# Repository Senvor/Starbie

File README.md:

<div align="center">

# Starbie

**A tiny motion-controlled digital pet, basically a desktop Tamagotchi. Totally not a Starboy.**

A star-shaped PCB pet you tilt, shake and feed, with an OLED face, a mood LED and two clicky switches.

</div>

---

## What is it?

Starbie is a small interactive device built around the XIAO ESP32-C3. It uses a bunch of sensors and other components to make it actually do stuff.

Some of the things packed into it:

- **Movement detection** using the MPU6050, so you steer the menu by tilting and play by shaking
- **Temperature and humidity** readings from the DHT11
- **An OLED display** for the pet, the menu and the stats
- **An RGB LED** that shows the pet's mood
- **Two mechanical switches** (Gateron Milky Pro Yellow with Cherry-style keycaps) for input
- **Stats saved to flash**, so your pet remembers you after a reset

## Why I Built It

I made Starbie for [HalfLife](https://halflife.hackclub.com), following their Week 1 PCB design tutorial.

Since this is my second hardware project, I wanted to build something a bit more interesting than my first one. Starbie is a tiny motion-controlled digital pet, basically a desktop Tamagotchi (totally not a Starboy).

And yeah, I'm also trying to get that 3D printer prize lol. HalfLife gives me a reason to actually design, build and document my projects instead of leaving them as ideas.

The full build log is in [JOURNAL.md](JOURNAL.md).

## The Schematic

The schematic was made in KiCad and shows how all the components are connected to the XIAO ESP32-C3.

<div align="center">

</div>

## The PCB Design

I designed the board using KiCad, with a custom shape and footprints for the components.

<div align="center">
  
</div>

## Fabrication

Here's the final manufacturing quote and preview from Robu before it becomes reality:

<div align="center">
    
</div>

## Firmware

The firmware is written for the XIAO ESP32-C3 and handles Starbie's sensors, display, RGB LED and buttons. It reads movement data from the MPU6050 and temperature and humidity from the DHT11, with the OLED used to display information.

### Wiring (pins)

| Part | XIAO pin | ESP32-C3 GPIO |
|---|---|---|
| OLED + MPU6050 SDA | D5 | 7 |
| OLED + MPU6050 SCL | D4 | 6 |
| DHT11 data | D1 | 3 |
| Button 1 | D2 | 4 |
| Button 2 | D3 | 5 |
| LED red | D0 | 2 |
| LED green | D6 | 21 |
| LED blue | D7 | 20 |

The RGB LED is common anode (tied to 3.3V), so the firmware drives a colour LOW to turn it on. The OLED is expected at I2C address `0x3C` and the MPU6050 at `0x68`.

### Controls

Starbie has two buttons.

| Button | Pin | What it does |
|---|---|---|
| Button 1 (SW1) | GPIO4 (XIAO D2) | Opens the radial menu. While the menu is open, it confirms the highlighted action. |
| Button 2 (SW2) | GPIO5 (XIAO D3) | Shows or hides the stats screen. It never changes the pet. |

Both buttons are debounced in software (30 ms).

### Tilt menu

1. Press **Button 1** to open the menu. The way you are holding Starbie at that moment becomes the centre.
2. Tilt Starbie. The MPU6050 accelerometer moves a ball around the screen. The screen is split into four sectors by two diagonal lines: **NAP** (top), **PLAY** (right), **FEED** (bottom) and **PET** (left).
3. The sector in the direction you tilt is highlighted. A small dead zone in the middle means nothing is highlighted until you tilt past it.
4. Press **Button 1** again to confirm. If nothing is highlighted, nothing happens and the menu stays open.
5. Pressing **Button 2** while the menu is open leaves the menu without choosing anything and shows the stats screen instead.

Which physical tilt direction moves the ball to which sector depends on how the MPU6050 is mounted. If the ball moves the wrong way, change `SWAP_MPU_AXES`, `MENU_X_DIRECTION` or `MENU_Y_DIRECTION` at the top of `Starbie.ino`.

Each action changes the pet's three stats (each stays between 0 and 100):

| Action | Joy | Energy | Fullness | What you see |
|---|---|---|---|---|
| NAP | +1 | +18 | −4 | Starbie stops and sleeps with floating Zs for 48 seconds |
| PLAY | +12 | −9 | −5 | Two fast laps across the screen with hearts |
| FEED | +3 | +2 | +18 | A small wiggle, then a jump |
| PET | +7 | 0 | 0 | A small wiggle, a jump, and hearts |

**Shake:** on the pet screen, shaking Starbie gives +5 joy, −2 energy and −1 fullness, wakes a sleeping pet, and has a 0.65 second cooldown. Shaking does nothing while the menu or stats screen is open.

Stats are saved to flash after every action and every shake, so Starbie remembers them after a reset. Stats do not drain over time; they only change when you use the menu or shake Starbie.

### Status LED

The RGB LED shows Starbie's mood. The firmware checks the stats in this order and shows the first one that matches:

| Colour | Condition | Meaning |
|---|---|---|
| Yellow | Fullness is 25 or below | Hungry |
| Blue | Energy is 25 or below | Tired |
| Red | Joy is 25 or below | Needs play |
| Green | None of the above (all three stats are above 25) | Happy |

If more than one stat is low, the first row that matches wins (yellow, then blue, then red). The LED is on/off only (no dimming or colour mixing), and yellow is red and green on together.

### Stats screen

Press **Button 2** to see Starbie's JOY, ENERGY and FULL bars with their numbers, plus the room temperature (°C) and humidity (%) from the DHT11. If the DHT11 has not produced a reading yet, the screen shows `--`. The temperature and humidity are display-only; they do not affect the pet or the LED.

## Getting Started

The firmware is one file, `Starbie.ino`.

1. Open `Starbie.ino` in the [Arduino IDE](https://www.arduino.cc/en/software) with ESP32 board support installed, and pick the **Seeed XIAO ESP32-C3** board.
2. Install these libraries from **Sketch > Include Library > Manage Libraries** (click **Install All** when it asks about dependencies):
   - Adafruit GFX Library
   - Adafruit SSD1306
   - Adafruit MPU6050
   - DHT sensor library
3. Change anything you want in the **BEGINNER SETTINGS** section at the top (pins, starting stats, tilt directions, the pet sprite).
4. Upload.

Want a fresh pet? Set `RESET_SAVED_PET_ON_BOOT` to `true`, upload once, then set it back to `false`.

## Bill Of Materials

Also in [BOM.csv](BOM.csv).

| Item | Qty | Supplier | Cost/item | Total Cost | Link |
|---|---:|---|---:|---:|---|
| XIAO ESP32-C3 | 1 | hubtronics | $7.17 | $7.17 | https://hubtronics.in/seeed-studio-xiao-esp32c3 |
| MPU-6050 GY-521 | 1 | hubtronics | $2.00 | $2.00 | https://hubtronics.in/gy-521-mpu-6050-gyro-accelerometer-module |
| 5mm RGB LED, 4-leg (pack of 5) | 1 | hubtronics | $0.32 | $0.32 | https://hubtronics.in/5mm-rgb-led-4-legs |
| 0.96-inch I2C OLED, white | 1 | hubtronics | $1.78 | $1.78 | https://hubtronics.in/0.96inch-i2c-4pin-oled-module-white |
| Blank translucent Cherry 1u keycaps (pack of 5) | 1 | meckeys | $1.36 | $1.36 | https://meckeys.com/shop/accessories/keyboard-accessories/keycaps/blank/blank-ch |
| Gateron Milky Pro Yellow 5-pin switches (pack of 10) | 1 | meckeys | $2.10 | $2.10 | https://meckeys.com/shop/accessories/keyboard-accessories/key-switches/gateron-mechanical-pro-switch-5pin/?attribute_pa_switch-variation=pro-milky-yellow |
| 330Ω, 1/8W resistor (pack of 42) | 1 | robu | $0.11 | $0.11 | https://robu.in/product/330-ohm-1-8w-through-hole-resistor-pack-of-5000/ |
| 10kΩ, 1/8W resistor (pack of 30) | 1 | robu | $0.11 | $0.11 | https://robu.in/product/10k-ohm-0-25w-metal-film-resistor-pack-of-100/ |
| DHT11 temperature and humidity sensor | 1 | robu | $1.57 | $1.57 | https://robu.in/product/dht-11-digital-temperature-and-humidity-sensor/ |
| Custom Starbie PCB | 1 | robu | $20.05 | $20.05 | https://robu.in/ |
| Total shipping | 1 | — | — | $2.38 | — |

## Tech Stack

- **KiCad** - schematic and PCB design
- **Robu** - PCB fabrication quote and preview
- **Arduino (C++)** - the firmware
- **Seeed XIAO ESP32-C3** - the brain
- **Adafruit GFX / SSD1306 / MPU6050 + DHT sensor library** - display and sensor drivers
- **Preferences (ESP32)** - saving the pet's stats to flash

## Project Structure

```
Starbie/
├── Starbie.ino       # the whole firmware, one file
├── pcb/              # KiCad project, schematic and PCB
├── output files/     # fabrication outputs (Starbie.zip)
├── assets/           # README images
├── BOM.csv           # bill of materials
└── JOURNAL.md        # devlog, synced from HalfLife
```

## What I Learned

From the journal:

- Importing custom symbols and footprints into KiCad, and assigning footprints to symbols
- Getting the schematic into the PCB editor (through the project manager) and fixing DRC errors like overlapping edge cuts
- Using vias to route on both layers instead of cramming everything onto the front copper
- Sourcing a BOM across multiple suppliers when no single shop has everything
- Swapping a part for one that's actually on the market and updating the PCB to match

## License

This project is licensed under the [MIT License](LICENSE). You're free to use, modify, and share it, as long as the original copyright notice is kept.

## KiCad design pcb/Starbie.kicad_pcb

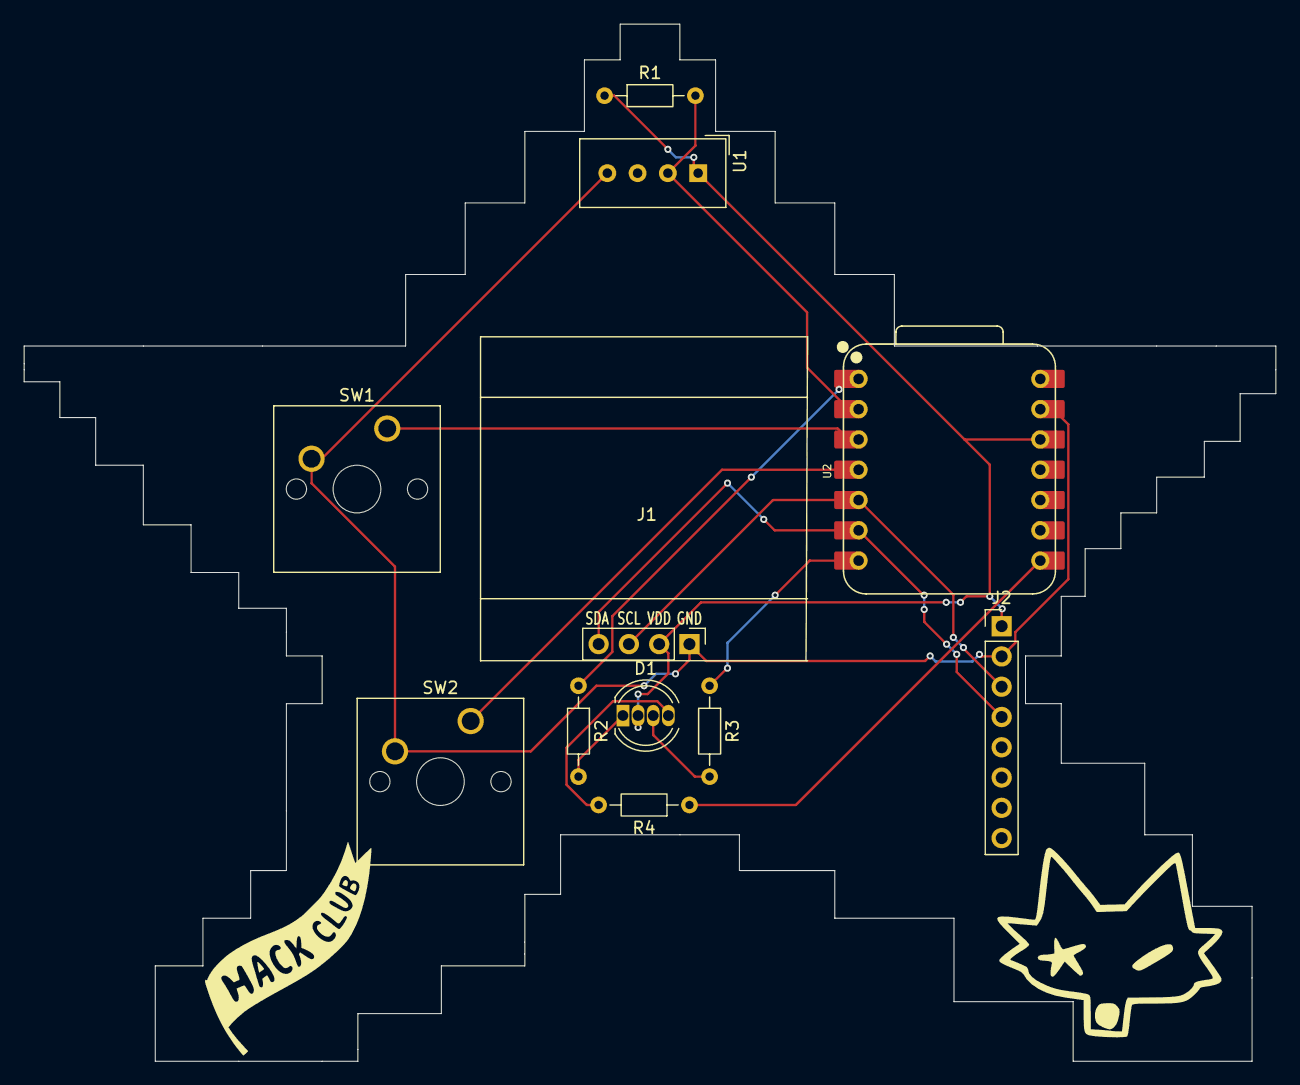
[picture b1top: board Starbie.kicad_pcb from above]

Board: 2 copper layers, 105.0 x 87.0 mm, 11 parts (0 on the bottom side), 13 nets.

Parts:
D1: LED_RGB; LED_D5.0mm-4_RGB
J1: Conn_01x04_Pin; Display_128x64_096_I2C
J2: Conn_01x08_Pin; PinHeader_1x08_P2.54mm_Vertical
R1: 10k; R_Axial_DIN0204_L3.6mm_D1.6mm_P7.62mm_Horizontal
R2, R3, R4: 330; R_Axial_DIN0204_L3.6mm_D1.6mm_P7.62mm_Horizontal
SW1, SW2: SW_Push; SW_Cherry_MX_1.00u_PCB
U1: DHT11; Aosong_DHT11_5.5x12.0_P2.54mm
U2: XIAO-ESP32-C3-SMD; XIAO-ESP32-C6-DIP

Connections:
+3.3V: D1.2 (A), J1.2, J2.1, R1.1, U1.1 (VDD), U2.12 (3V3_OUT)
/DHT11 DATA: R1.2, U1.2 (DATA), U2.2 (D1)
/GPIO2: SW1.1, U2.3 (D2)
/GPIO3: SW2.1, U2.4 (D3)
/LED_B: R4.1, U2.8 (D7)
/LED_G: R3.1, U2.7 (D6)
/LED_R: R2.1, U2.1 (D0)
/SCL: J1.3, J2.3, U2.5 (D4)
/SDA: J1.4, J2.4, U2.6 (D5)
GND: J1.1, J2.2, SW1.2, SW2.2, U1.4 (GND), U2.13 (GND)
unnamed: D1.4 (BK), R4.2
unnamed: D1.3 (GK), R3.2
unnamed: D1.1 (RK), R2.2
